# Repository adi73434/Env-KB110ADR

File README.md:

# Env-KB110ADR
A 110% keyboard made for a friend who wanted something for work.

This also uses a raspberry pi pico but with a MCP23017 as the pi pico doesnt have enough exposed pins.

- Project Name: Env-KB110ADR
- Nickname: Victus

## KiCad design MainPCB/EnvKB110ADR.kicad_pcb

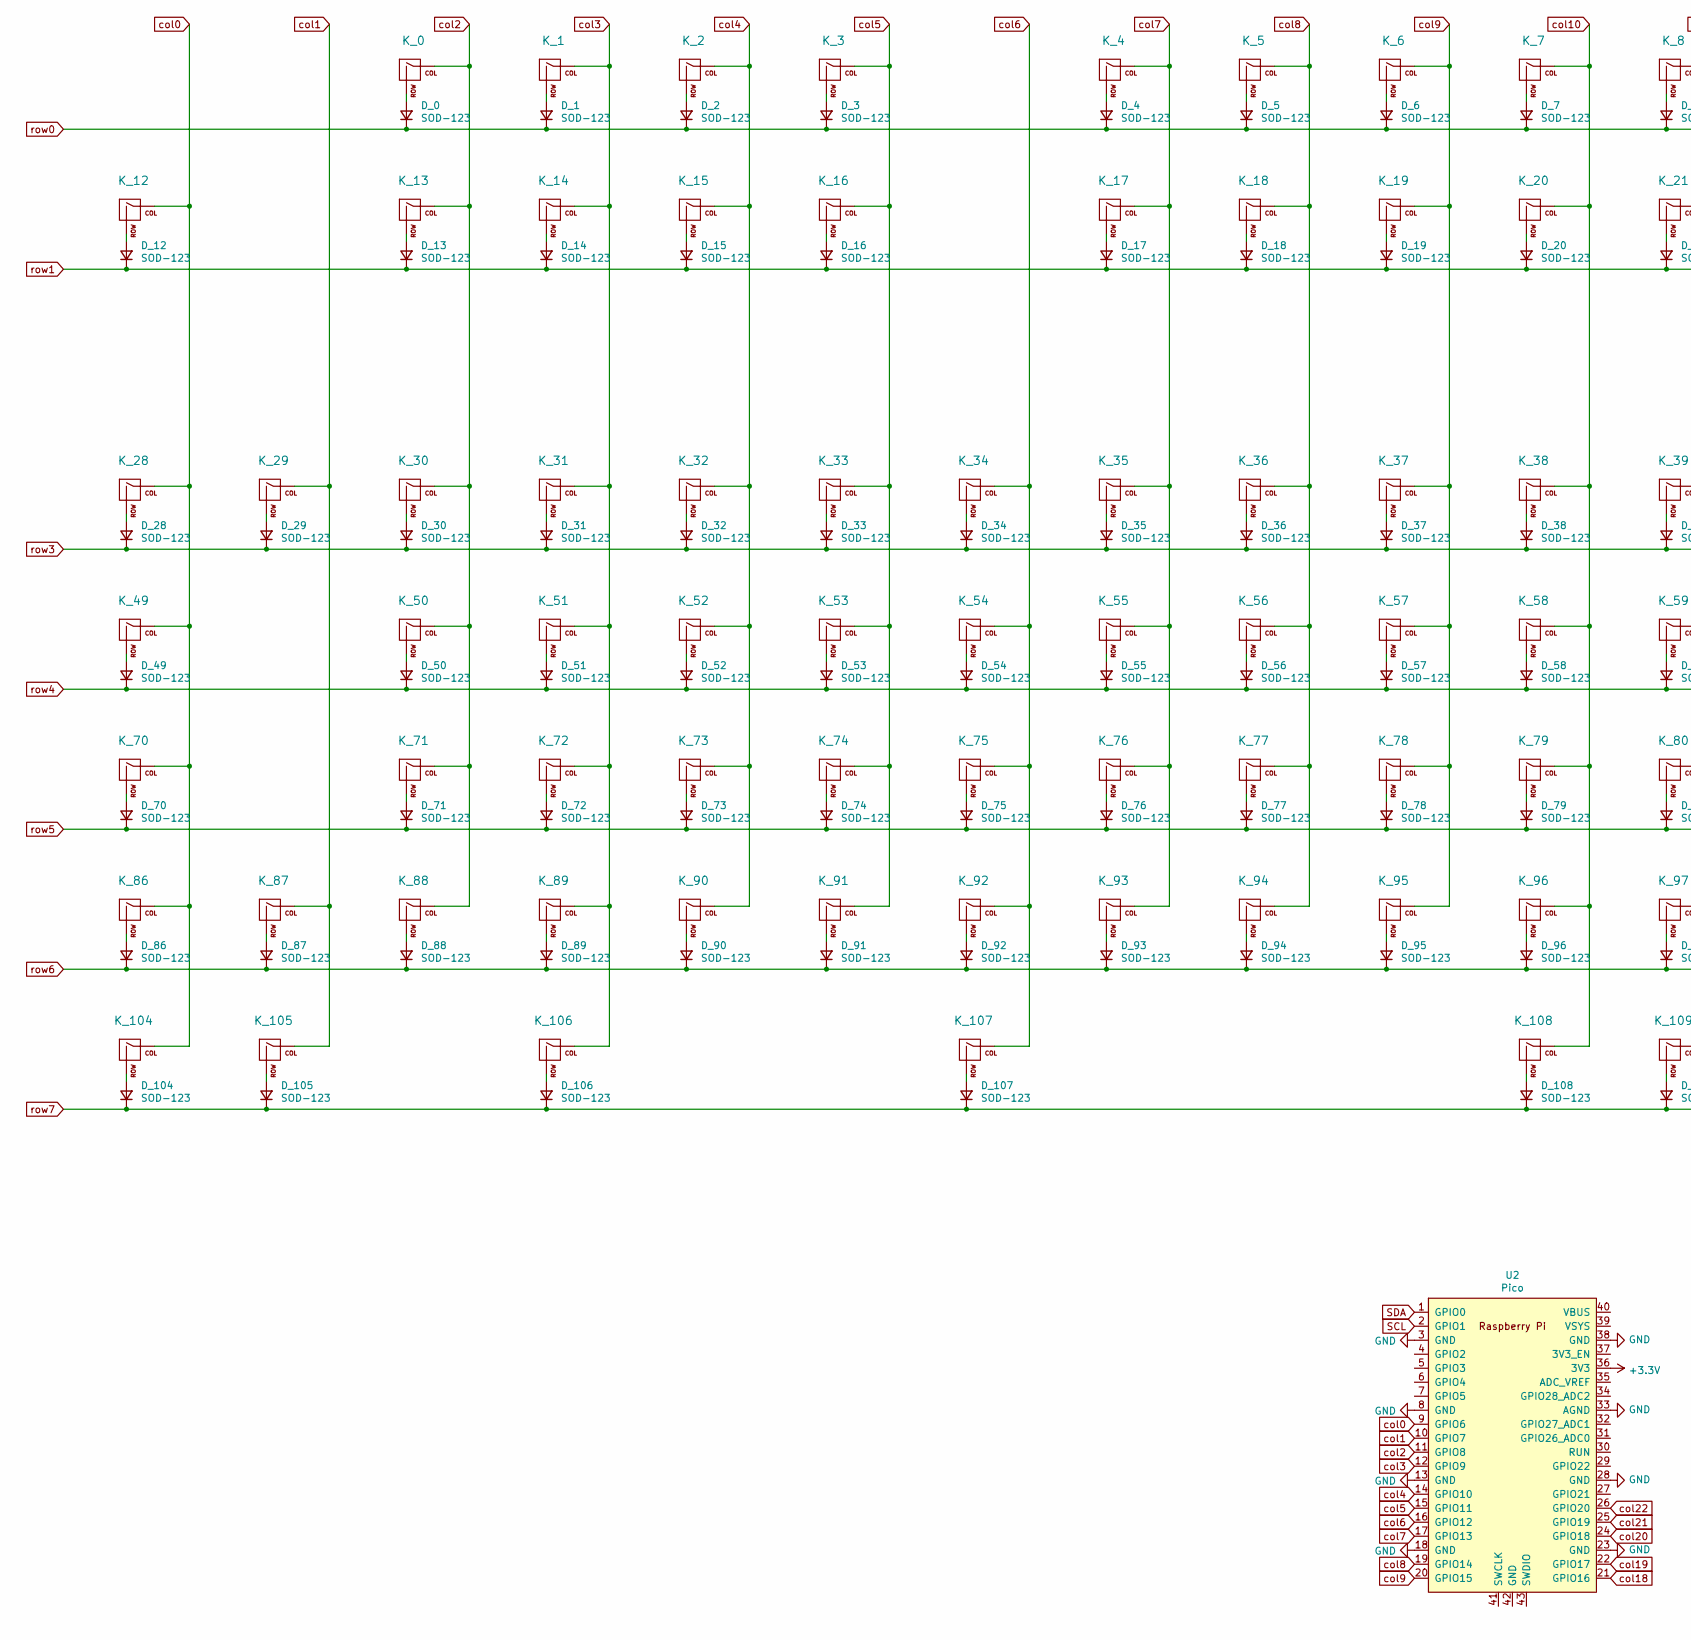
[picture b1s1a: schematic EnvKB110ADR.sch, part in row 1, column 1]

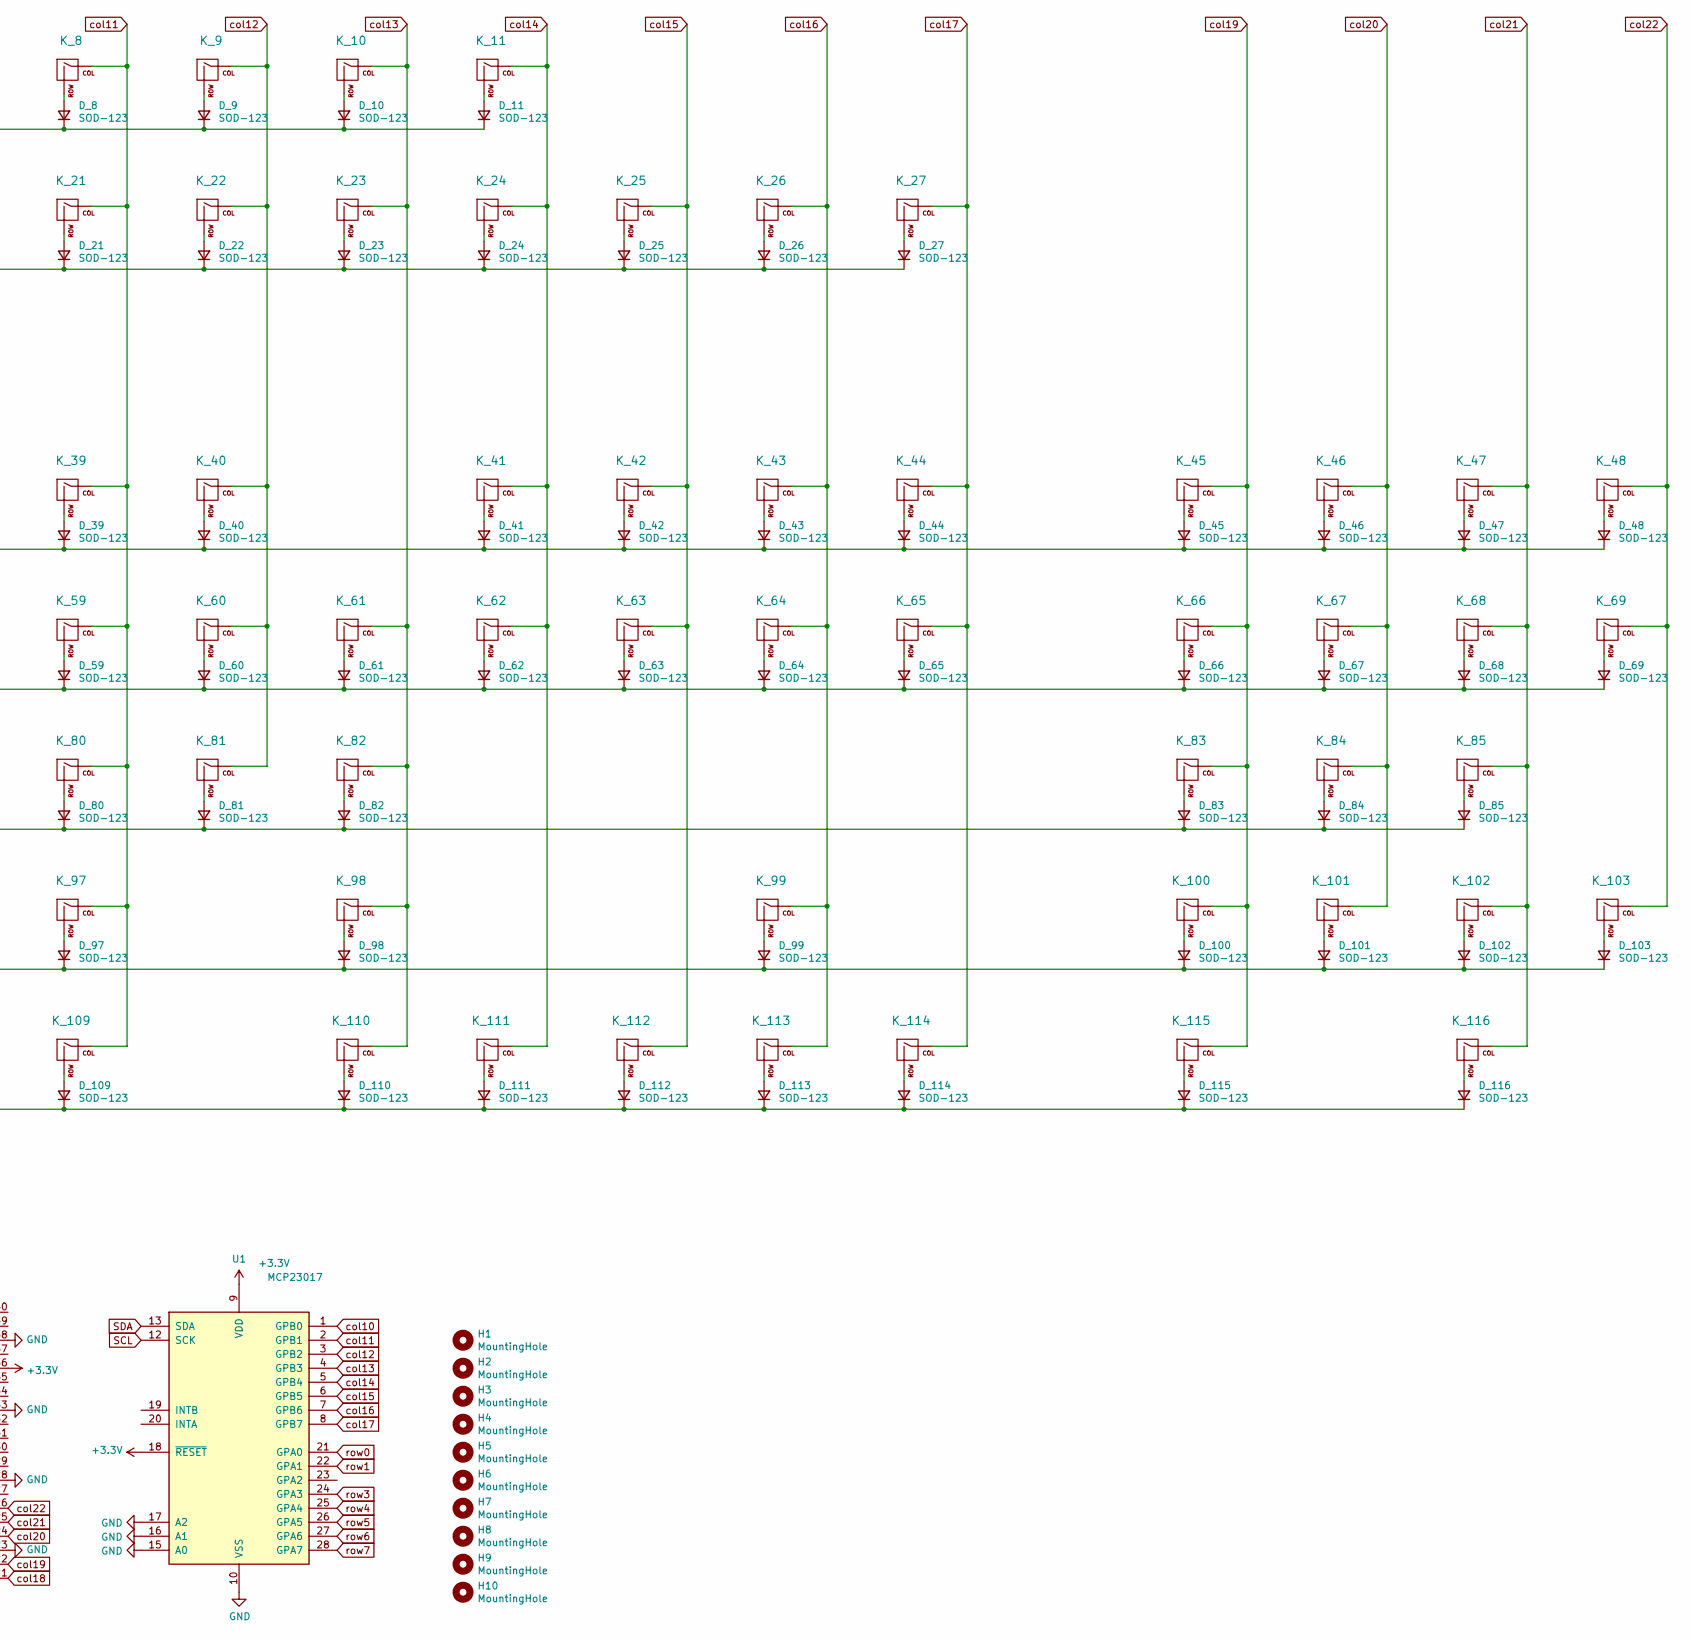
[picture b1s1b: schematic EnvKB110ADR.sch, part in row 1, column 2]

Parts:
D_0, D_1, D_2, D_3, D_4, D_5, D_6, D_7, D_8, D_9, D_10, D_11, D_12, D_13, D_14, D_15, D_16, D_17, D_18, D_19, D_20, D_21, D_22, D_23, D_24, D_25, D_26, D_27, D_28, D_29, D_30, D_31, D_32, D_33, D_34, D_35, D_36, D_37, D_38, D_39, D_40, D_41, D_42, D_43, D_44, D_45, D_46, D_47, D_48, D_49, D_50, D_51, D_52, D_53, D_54, D_55, D_56, D_57, D_58, D_59, D_60, D_61, D_62, D_63, D_64, D_65, D_66, D_67, D_68, D_69, D_70, D_71, D_72, D_73, D_74, D_75, D_76, D_77, D_78, D_79, D_80, D_81, D_82, D_83, D_84, D_85, D_86, D_87, D_88, D_89, D_90, D_91, D_92, D_93, D_94, D_95, D_96, D_97, D_98, D_99, D_100, D_101, D_102, D_103, D_104, D_105, D_106, D_107, D_108, D_109, D_110, D_111, D_112, D_113, D_114, D_115, D_116: SOD-123; D_SOD-123
H1, H2, H3, H4, H5, H6, H7, H8, H9, H10: MountingHole; MountingHole_2.2mm_M2
K_0, K_1, K_2, K_3, K_4, K_5, K_6, K_7, K_8, K_9, K_10, K_11, K_12, K_13, K_14, K_15, K_16, K_17, K_18, K_19, K_20, K_21, K_22, K_23, K_24, K_25, K_26, K_27, K_28, K_29, K_30, K_31, K_32, K_33, K_34, K_35, K_36, K_37, K_38, K_39, K_40, K_42, K_43, K_44, K_45, K_46, K_47, K_48, K_50, K_51, K_52, K_53, K_54, K_55, K_56, K_57, K_58, K_59, K_60, K_61, K_63, K_64, K_65, K_66, K_67, K_68, K_71, K_72, K_73, K_74, K_75, K_76, K_77, K_78, K_79, K_80, K_81, K_82, K_83, K_84, K_85, K_87, K_88, K_89, K_90, K_91, K_92, K_93, K_94, K_95, K_96, K_97, K_99, K_100, K_101, K_102, K_112, K_113, K_114, K_116: KEYSW; MXOnly-1U-Hotswap
K_41, K_62, K_69, K_103, K_115: KEYSW; MXOnly-2U-Hotswap
K_49: KEYSW; MXOnly-1.5U-Hotswap
K_70: KEYSW; MXOnly-1.75U-Hotswap
K_86, K_104, K_105, K_106, K_108, K_109, K_110, K_111: KEYSW; MXOnly-1.25U-Hotswap
K_98: KEYSW; MXOnly-2.75U-Hotswap
K_107: KEYSW; MXOnly-6.25U-Hotswap-ReversedStabilizers
U1: MCP23017; SOIC-28W_7.5x17.9mm_P1.27mm; LCSC MCP23017_SO
U2: Pico; RPi_Pico_SMD_TH

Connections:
+3V3: U1.9 (VDD), U1.18 (~RESET~), U2.36 (3V3)
GND: U1.10 (VSS), U1.15 (A0), U1.16 (A1), U1.17 (A2), U2.3 (GND), U2.8 (GND), U2.13 (GND), U2.18 (GND), U2.23 (GND), U2.28 (GND), U2.33 (AGND), U2.38 (GND)
unnamed: D_0.2 (A), K_0.2 (ROW)
unnamed: D_1.2 (A), K_1.2 (ROW)
unnamed: D_2.2 (A), K_2.2 (ROW)
unnamed: D_3.2 (A), K_3.2 (ROW)
unnamed: D_4.2 (A), K_4.2 (ROW)
unnamed: D_5.2 (A), K_5.2 (ROW)
unnamed: D_6.2 (A), K_6.2 (ROW)
unnamed: D_7.2 (A), K_7.2 (ROW)
unnamed: D_8.2 (A), K_8.2 (ROW)
unnamed: D_9.2 (A), K_9.2 (ROW)
unnamed: D_10.2 (A), K_10.2 (ROW)
unnamed: D_11.2 (A), K_11.2 (ROW)
unnamed: D_12.2 (A), K_12.2 (ROW)
unnamed: D_13.2 (A), K_13.2 (ROW)
unnamed: D_14.2 (A), K_14.2 (ROW)
unnamed: D_15.2 (A), K_15.2 (ROW)
unnamed: D_16.2 (A), K_16.2 (ROW)
unnamed: D_17.2 (A), K_17.2 (ROW)
unnamed: D_18.2 (A), K_18.2 (ROW)
unnamed: D_19.2 (A), K_19.2 (ROW)
unnamed: D_20.2 (A), K_20.2 (ROW)
unnamed: D_21.2 (A), K_21.2 (ROW)
unnamed: D_22.2 (A), K_22.2 (ROW)
unnamed: D_23.2 (A), K_23.2 (ROW)
unnamed: D_24.2 (A), K_24.2 (ROW)
unnamed: D_25.2 (A), K_25.2 (ROW)
unnamed: D_26.2 (A), K_26.2 (ROW)
unnamed: D_27.2 (A), K_27.2 (ROW)
unnamed: D_28.2 (A), K_28.2 (ROW)
unnamed: D_29.2 (A), K_29.2 (ROW)
unnamed: D_30.2 (A), K_30.2 (ROW)
unnamed: D_31.2 (A), K_31.2 (ROW)
unnamed: D_32.2 (A), K_32.2 (ROW)
unnamed: D_33.2 (A), K_33.2 (ROW)
unnamed: D_34.2 (A), K_34.2 (ROW)
unnamed: D_35.2 (A), K_35.2 (ROW)
unnamed: D_36.2 (A), K_36.2 (ROW)
unnamed: D_37.2 (A), K_37.2 (ROW)
unnamed: D_38.2 (A), K_38.2 (ROW)
unnamed: D_39.2 (A), K_39.2 (ROW)
unnamed: D_40.2 (A), K_40.2 (ROW)
unnamed: D_41.2 (A), K_41.2 (ROW)
unnamed: D_42.2 (A), K_42.2 (ROW)
unnamed: D_43.2 (A), K_43.2 (ROW)
unnamed: D_44.2 (A), K_44.2 (ROW)
unnamed: D_45.2 (A), K_45.2 (ROW)
unnamed: D_46.2 (A), K_46.2 (ROW)
unnamed: D_47.2 (A), K_47.2 (ROW)
unnamed: D_48.2 (A), K_48.2 (ROW)
unnamed: D_49.2 (A), K_49.2 (ROW)
unnamed: D_50.2 (A), K_50.2 (ROW)
unnamed: D_51.2 (A), K_51.2 (ROW)
unnamed: D_52.2 (A), K_52.2 (ROW)
unnamed: D_53.2 (A), K_53.2 (ROW)
unnamed: D_54.2 (A), K_54.2 (ROW)
unnamed: D_55.2 (A), K_55.2 (ROW)
unnamed: D_56.2 (A), K_56.2 (ROW)
unnamed: D_57.2 (A), K_57.2 (ROW)
unnamed: D_58.2 (A), K_58.2 (ROW)
unnamed: D_59.2 (A), K_59.2 (ROW)
unnamed: D_60.2 (A), K_60.2 (ROW)
unnamed: D_61.2 (A), K_61.2 (ROW)
unnamed: D_62.2 (A), K_62.2 (ROW)
unnamed: D_63.2 (A), K_63.2 (ROW)
unnamed: D_64.2 (A), K_64.2 (ROW)
unnamed: D_65.2 (A), K_65.2 (ROW)
unnamed: D_66.2 (A), K_66.2 (ROW)
unnamed: D_67.2 (A), K_67.2 (ROW)
unnamed: D_68.2 (A), K_68.2 (ROW)
unnamed: D_69.2 (A), K_69.2 (ROW)
unnamed: D_70.2 (A), K_70.2 (ROW)
unnamed: D_71.2 (A), K_71.2 (ROW)
unnamed: D_72.2 (A), K_72.2 (ROW)
unnamed: D_73.2 (A), K_73.2 (ROW)
unnamed: D_74.2 (A), K_74.2 (ROW)
unnamed: D_75.2 (A), K_75.2 (ROW)
unnamed: D_76.2 (A), K_76.2 (ROW)
unnamed: D_77.2 (A), K_77.2 (ROW)
unnamed: D_78.2 (A), K_78.2 (ROW)
unnamed: D_79.2 (A), K_79.2 (ROW)
unnamed: D_80.2 (A), K_80.2 (ROW)
unnamed: D_81.2 (A), K_81.2 (ROW)
unnamed: D_82.2 (A), K_82.2 (ROW)
unnamed: D_83.2 (A), K_83.2 (ROW)
unnamed: D_84.2 (A), K_84.2 (ROW)
unnamed: D_85.2 (A), K_85.2 (ROW)
unnamed: D_86.2 (A), K_86.2 (ROW)
unnamed: D_87.2 (A), K_87.2 (ROW)
unnamed: D_88.2 (A), K_88.2 (ROW)
unnamed: D_89.2 (A), K_89.2 (ROW)
unnamed: D_90.2 (A), K_90.2 (ROW)
unnamed: D_91.2 (A), K_91.2 (ROW)
unnamed: D_92.2 (A), K_92.2 (ROW)
unnamed: D_93.2 (A), K_93.2 (ROW)
unnamed: D_94.2 (A), K_94.2 (ROW)
unnamed: D_95.2 (A), K_95.2 (ROW)
unnamed: D_96.2 (A), K_96.2 (ROW)
unnamed: D_97.2 (A), K_97.2 (ROW)
unnamed: D_98.2 (A), K_98.2 (ROW)
unnamed: D_99.2 (A), K_99.2 (ROW)
unnamed: D_100.2 (A), K_100.2 (ROW)
unnamed: D_101.2 (A), K_101.2 (ROW)
unnamed: D_102.2 (A), K_102.2 (ROW)
unnamed: D_103.2 (A), K_103.2 (ROW)
unnamed: D_104.2 (A), K_104.2 (ROW)
unnamed: D_105.2 (A), K_105.2 (ROW)
unnamed: D_106.2 (A), K_106.2 (ROW)
unnamed: D_107.2 (A), K_107.2 (ROW)
unnamed: D_108.2 (A), K_108.2 (ROW)
unnamed: D_109.2 (A), K_109.2 (ROW)
unnamed: D_110.2 (A), K_110.2 (ROW)
unnamed: D_111.2 (A), K_111.2 (ROW)
unnamed: D_112.2 (A), K_112.2 (ROW)
unnamed: D_113.2 (A), K_113.2 (ROW)
unnamed: D_114.2 (A), K_114.2 (ROW)
unnamed: D_115.2 (A), K_115.2 (ROW)
unnamed: D_116.2 (A), K_116.2 (ROW)
SCL: U1.12 (SCK), U2.2 (GPIO1)
SDA: U1.13 (SDA), U2.1 (GPIO0)
col0: K_12.1 (COL), K_28.1 (COL), K_49.1 (COL), K_70.1 (COL), K_86.1 (COL), K_104.1 (COL), U2.9 (GPIO6)
col1: K_29.1 (COL), K_87.1 (COL), K_105.1 (COL), U2.10 (GPIO7)
col2: K_0.1 (COL), K_13.1 (COL), K_30.1 (COL), K_50.1 (COL), K_71.1 (COL), K_88.1 (COL), U2.11 (GPIO8)
col3: K_1.1 (COL), K_14.1 (COL), K_31.1 (COL), K_51.1 (COL), K_72.1 (COL), K_89.1 (COL), K_106.1 (COL), U2.12 (GPIO9)
col4: K_2.1 (COL), K_15.1 (COL), K_32.1 (COL), K_52.1 (COL), K_73.1 (COL), K_90.1 (COL), U2.14 (GPIO10)
col5: K_3.1 (COL), K_16.1 (COL), K_33.1 (COL), K_53.1 (COL), K_74.1 (COL), K_91.1 (COL), U2.15 (GPIO11)
col6: K_34.1 (COL), K_54.1 (COL), K_75.1 (COL), K_92.1 (COL), K_107.1 (COL), U2.16 (GPIO12)
col7: K_4.1 (COL), K_17.1 (COL), K_35.1 (COL), K_55.1 (COL), K_76.1 (COL), K_93.1 (COL), U2.17 (GPIO13)
col8: K_5.1 (COL), K_18.1 (COL), K_36.1 (COL), K_56.1 (COL), K_77.1 (COL), K_94.1 (COL), U2.19 (GPIO14)
col9: K_6.1 (COL), K_19.1 (COL), K_37.1 (COL), K_57.1 (COL), K_78.1 (COL), K_95.1 (COL), U2.20 (GPIO15)
col10: K_7.1 (COL), K_20.1 (COL), K_38.1 (COL), K_58.1 (COL), K_79.1 (COL), K_96.1 (COL), K_108.1 (COL), U1.1 (GPB0)
col11: K_8.1 (COL), K_21.1 (COL), K_39.1 (COL), K_59.1 (COL), K_80.1 (COL), K_97.1 (COL), K_109.1 (COL), U1.2 (GPB1)
col12: K_9.1 (COL), K_22.1 (COL), K_40.1 (COL), K_60.1 (COL), K_81.1 (COL), U1.3 (GPB2)
col13: K_10.1 (COL), K_23.1 (COL), K_61.1 (COL), K_82.1 (COL), K_98.1 (COL), K_110.1 (COL), U1.4 (GPB3)
col14: K_11.1 (COL), K_24.1 (COL), K_41.1 (COL), K_62.1 (COL), K_111.1 (COL), U1.5 (GPB4)
col15: K_25.1 (COL), K_42.1 (COL), K_63.1 (COL), K_112.1 (COL), U1.6 (GPB5)
col16: K_26.1 (COL), K_43.1 (COL), K_64.1 (COL), K_99.1 (COL), K_113.1 (COL), U1.7 (GPB6)
col17: K_27.1 (COL), K_44.1 (COL), K_65.1 (COL), K_114.1 (COL), U1.8 (GPB7)
col18: U2.21 (GPIO16)
col19: K_45.1 (COL), K_66.1 (COL), K_83.1 (COL), K_100.1 (COL), K_115.1 (COL), U2.22 (GPIO17)
col20: K_46.1 (COL), K_67.1 (COL), K_84.1 (COL), K_101.1 (COL), U2.24 (GPIO18)
col21: K_47.1 (COL), K_68.1 (COL), K_85.1 (COL), K_102.1 (COL), K_116.1 (COL), U2.25 (GPIO19)
col22: K_48.1 (COL), K_69.1 (COL), K_103.1 (COL), U2.26 (GPIO20)
row0: D_0.1 (K), D_1.1 (K), D_2.1 (K), D_3.1 (K), D_4.1 (K), D_5.1 (K), D_6.1 (K), D_7.1 (K), D_8.1 (K), D_9.1 (K), D_10.1 (K), D_11.1 (K), U1.21 (GPA0)
row1: D_12.1 (K), D_13.1 (K), D_14.1 (K), D_15.1 (K), D_16.1 (K), D_17.1 (K), D_18.1 (K), D_19.1 (K), D_20.1 (K), D_21.1 (K), D_22.1 (K), D_23.1 (K), D_24.1 (K), D_25.1 (K), D_26.1 (K), D_27.1 (K), U1.22 (GPA1)
row3: D_28.1 (K), D_29.1 (K), D_30.1 (K), D_31.1 (K), D_32.1 (K), D_33.1 (K), D_34.1 (K), D_35.1 (K), D_36.1 (K), D_37.1 (K), D_38.1 (K), D_39.1 (K), D_40.1 (K), D_41.1 (K), D_42.1 (K), D_43.1 (K), D_44.1 (K), D_45.1 (K), D_46.1 (K), D_47.1 (K), D_48.1 (K), U1.24 (GPA3)
row4: D_49.1 (K), D_50.1 (K), D_51.1 (K), D_52.1 (K), D_53.1 (K), D_54.1 (K), D_55.1 (K), D_56.1 (K), D_57.1 (K), D_58.1 (K), D_59.1 (K), D_60.1 (K), D_61.1 (K), D_62.1 (K), D_63.1 (K), D_64.1 (K), D_65.1 (K), D_66.1 (K), D_67.1 (K), D_68.1 (K), D_69.1 (K), U1.25 (GPA4)
row5: D_70.1 (K), D_71.1 (K), D_72.1 (K), D_73.1 (K), D_74.1 (K), D_75.1 (K), D_76.1 (K), D_77.1 (K), D_78.1 (K), D_79.1 (K), D_80.1 (K), D_81.1 (K), D_82.1 (K), D_83.1 (K), D_84.1 (K), D_85.1 (K), U1.26 (GPA5)
row6: D_86.1 (K), D_87.1 (K), D_88.1 (K), D_89.1 (K), D_90.1 (K), D_91.1 (K), D_92.1 (K), D_93.1 (K), D_94.1 (K), D_95.1 (K), D_96.1 (K), D_97.1 (K), D_98.1 (K), D_99.1 (K), D_100.1 (K), D_101.1 (K), D_102.1 (K), D_103.1 (K), U1.27 (GPA6)
row7: D_104.1 (K), D_105.1 (K), D_106.1 (K), D_107.1 (K), D_108.1 (K), D_109.1 (K), D_110.1 (K), D_111.1 (K), D_112.1 (K), D_113.1 (K), D_114.1 (K), D_115.1 (K), D_116.1 (K), U1.28 (GPA7)

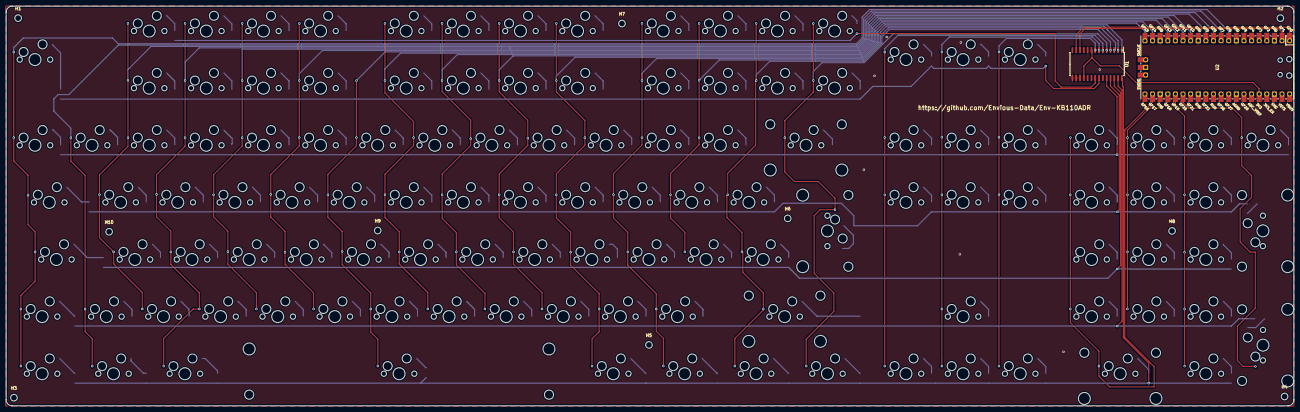
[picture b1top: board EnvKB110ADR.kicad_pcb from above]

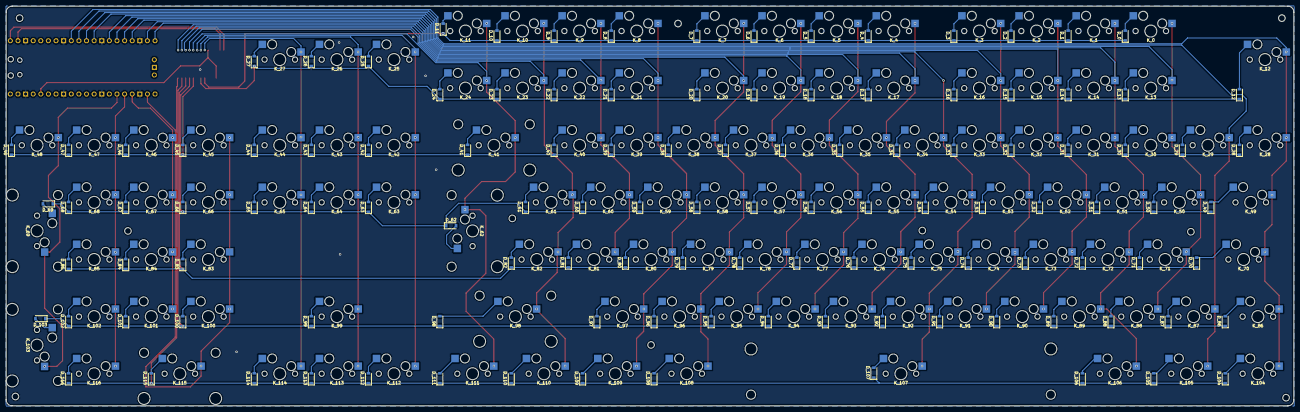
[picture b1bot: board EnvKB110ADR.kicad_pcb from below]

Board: 2 copper layers, 429.5 x 133.3 mm, 246 parts (117 on the bottom side), 150 nets.

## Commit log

2021-06-15 Added KiCad files.
2021-06-15 Created Backing PCB and added 10 M2 Mount holes
2021-06-15 Generated Switch Plate and cleaned up extras
2021-06-15 Added Logo and couple small corrections to traces.
2021-06-15 whatamidoing
